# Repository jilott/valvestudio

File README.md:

# valvestudio
All tube projects, laboratory assignments, experiments, etc are here. Go Valves Baby!

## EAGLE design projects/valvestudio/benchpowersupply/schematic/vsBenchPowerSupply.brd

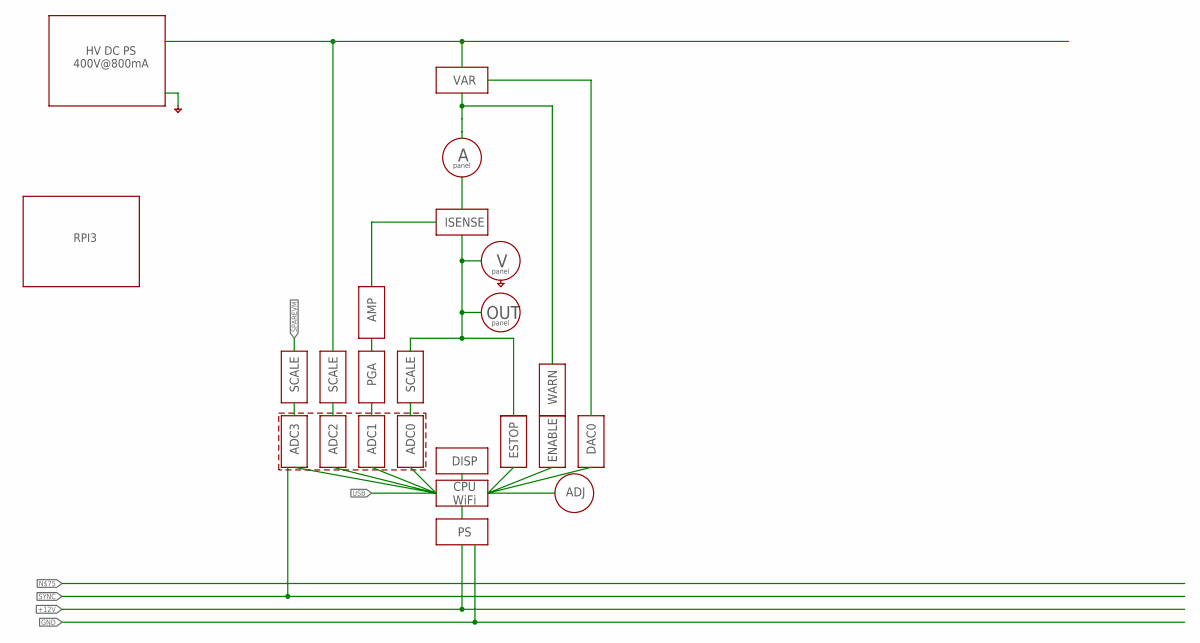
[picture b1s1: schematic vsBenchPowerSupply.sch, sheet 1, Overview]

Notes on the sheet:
HV DC PS 400V@800mA
RPI3
ISENSE
OUT
VAR
DAC0
AMP
ADC1
SCALE
ADC0
WARN
ENABLE
ESTOP
CPU WiFi
ADJ
DISP
ADC3
ADC2
PGA
panel

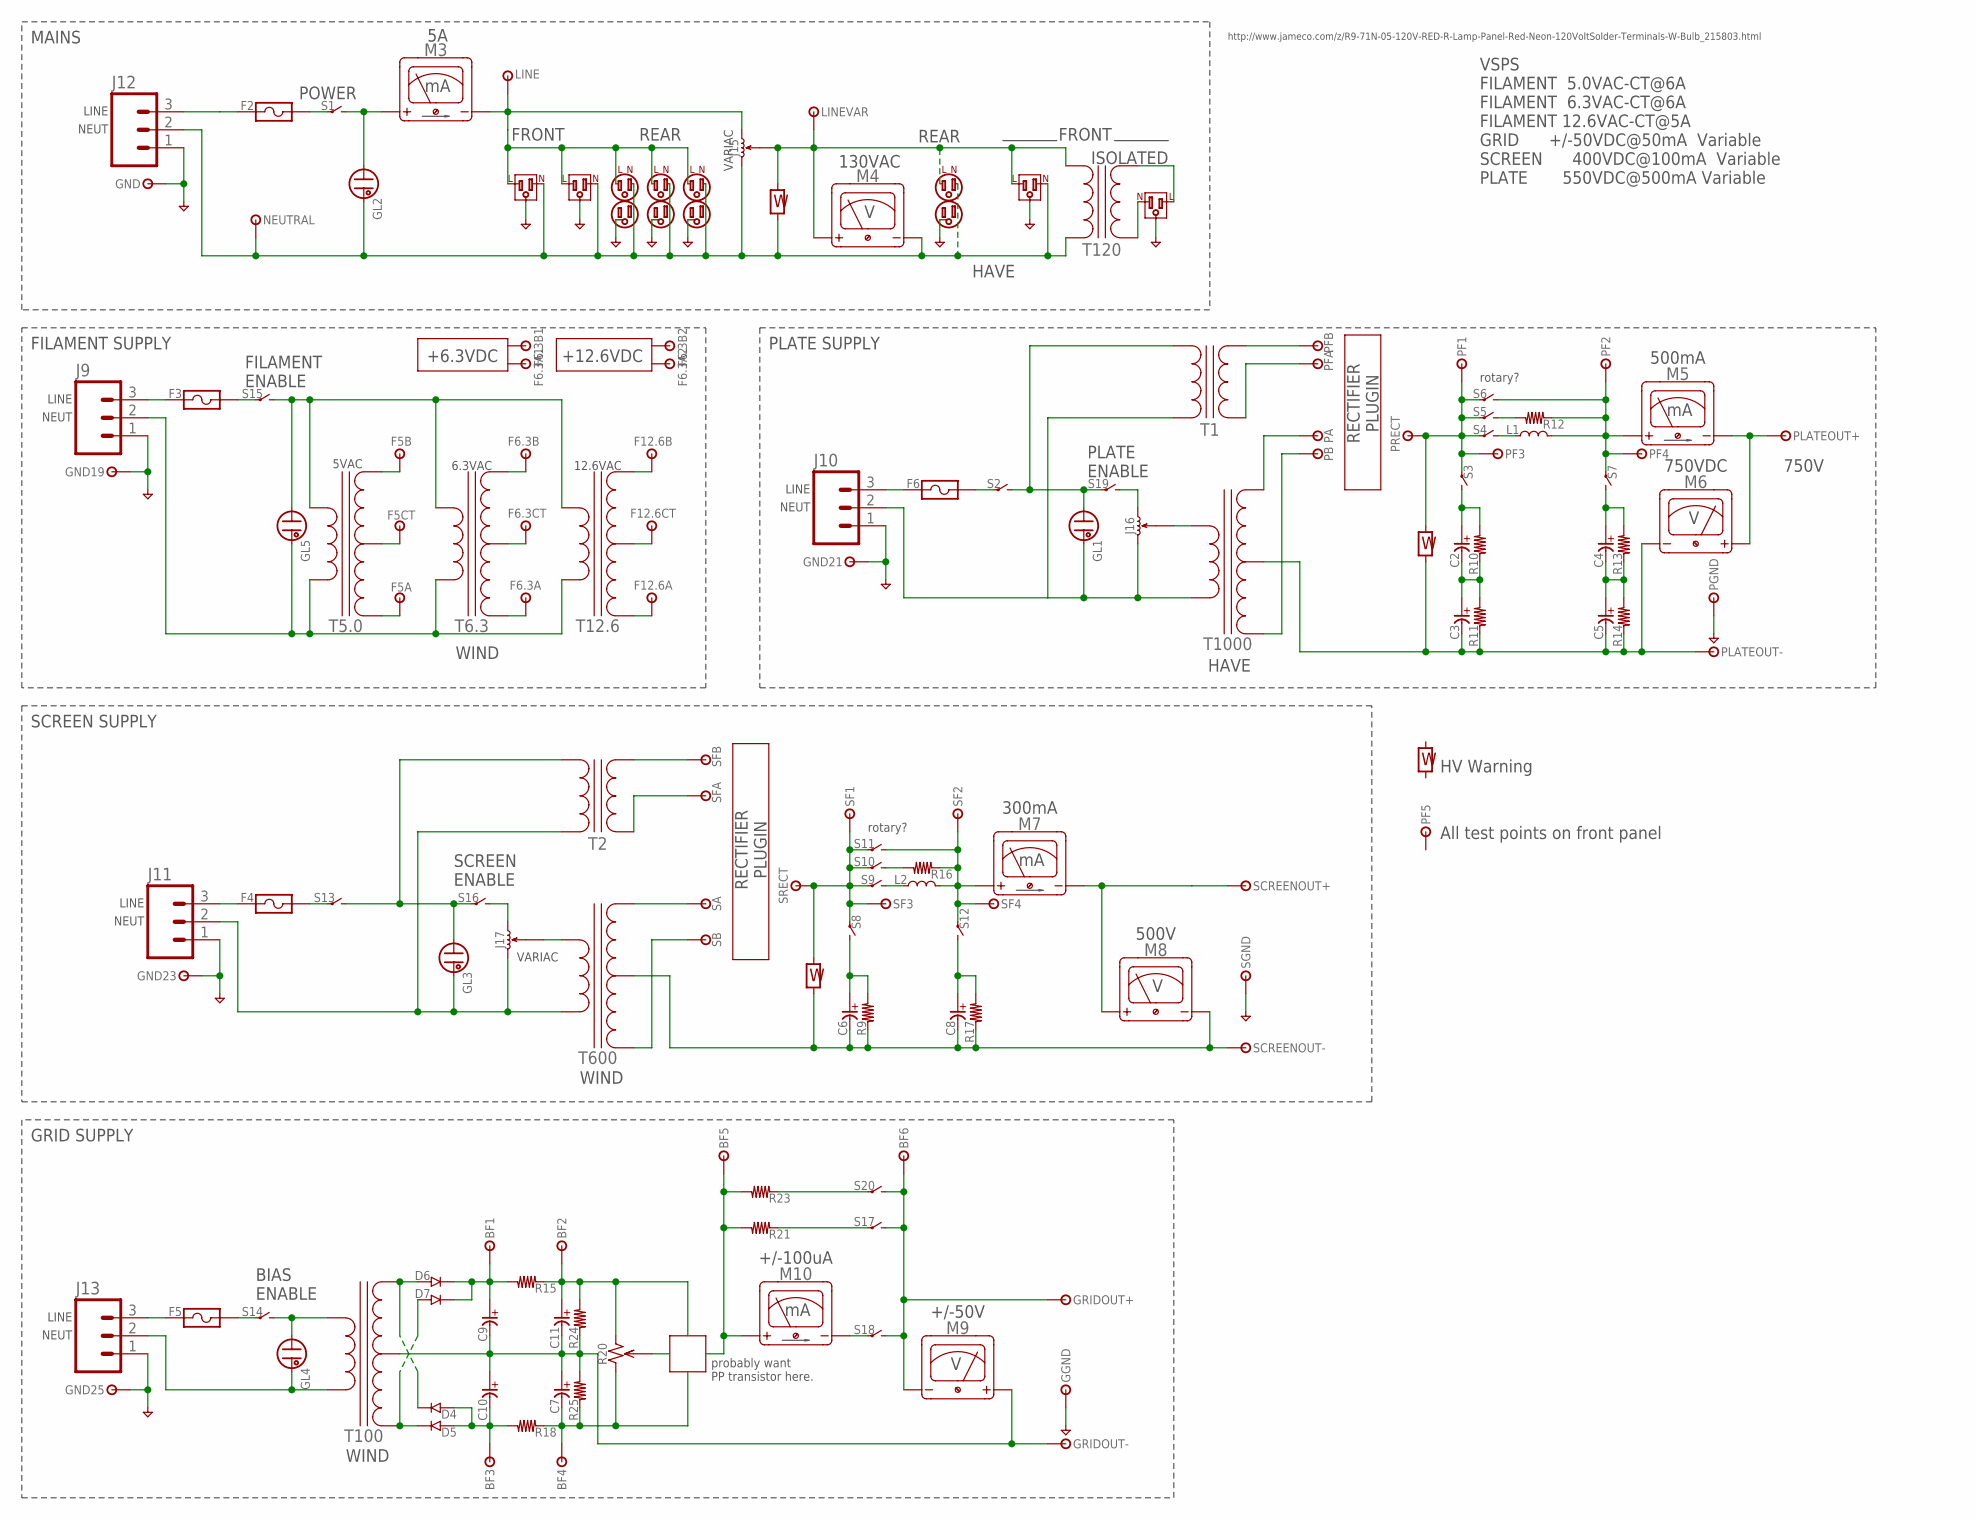
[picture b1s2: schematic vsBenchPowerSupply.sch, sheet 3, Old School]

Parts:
BF1, BF2, BF3, BF4, BF5, BF6: TESTPOINTTHRU; TPTHRU
C2, C3, C4, C5, C6, C7, C8, C9, C10, C11: C-POLARIZED-SMD-E-3MM; E-3
D4, D5, D6, D7: DIODE-1N4148; DO-35
F2, F3, F4, F5, F6: FUSE-HOLDER-3557-2; 3557-2
F5A, F5B, F5CT, F6.3A, F6.3A1, F6.3A2, F6.3B, F6.3B1, F6.3B2, F6.3CT, F12.6A, F12.6B, F12.6CT: TESTPOINTTHRU; TPTHRU
GGND: TESTPOINTTHRU; TPTHRU
GL1, GL2, GL3, GL4, GL5: INDICATOR-NEON-BULB-NE2-DRILL; NE2-NEON-BULB-DRILL
GND, GND19, GND21, GND23, GND25: TESTPOINTTHRU; TPTHRU
GRIDOUT+: TESTPOINTTHRU; TPTHRU
GRIDOUT-: TESTPOINTTHRU; TPTHRU
J3, J4, J5, J18: OUTLET-RECEPTABLE-SINGLE; CONN-3.81MM-KF2EDG-3
J6, J7, J8, J14: METER-PANEL-HV-WARNING; CONN-.100-2
J9, J10, J11, J12, J13: CONN-03-3.81MM-PLUGIN-SCREW; CONN-3.81MM-KF2EDG-3
J15, J16, J17: VARIAC; CONN-.100-3
L1, L2: INDUCTOR-0805; R0805
LINE: TESTPOINTTHRU; TPTHRU
LINEVAR: TESTPOINTTHRU; TPTHRU
M3, M5, M7, M10: METER-PANEL-ANALOG-CURRENT-PLUGIN-3.81MM; CONN-3.81MM-KF2EDG-2
M4, M6, M8, M9: METER-PANEL-ANALOG-VOLTAGE-PLUGIN-3.81MM; CONN-3.81MM-KF2EDG-2
NEUTRAL: TESTPOINTTHRU; TPTHRU
PA: TESTPOINTTHRU; TPTHRU
PB: TESTPOINTTHRU; TPTHRU
PF1, PF2, PF3, PF4, PF5: TESTPOINTTHRU; TPTHRU
PFA: TESTPOINTTHRU; TPTHRU
PFB: TESTPOINTTHRU; TPTHRU
PGND: TESTPOINTTHRU; TPTHRU
PLATEOUT+: TESTPOINTTHRU; TPTHRU
PLATEOUT-: TESTPOINTTHRU; TPTHRU
PRECT: TESTPOINTTHRU; TPTHRU
R9, R10, R11, R12, R13, R14, R15, R16, R17, R18, R21, R23, R24, R25: R-0402; R0402
R20: POTENTIOMETER; CONN-.100-3
S1, S2, S3, S4, S5, S6, S7, S8, S9, S10, S11, S12, S13, S14, S15, S16, S17, S18, S19, S20: SWITCH-PANEL-SPST; CONN-.100-2
SA: TESTPOINTTHRU; TPTHRU
SB: TESTPOINTTHRU; TPTHRU
SCREENOUT+: TESTPOINTTHRU; TPTHRU
SCREENOUT-: TESTPOINTTHRU; TPTHRU
SF1, SF2, SF3, SF4: TESTPOINTTHRU; TPTHRU
SFA: TESTPOINTTHRU; TPTHRU
SFB: TESTPOINTTHRU; TPTHRU
SGND: TESTPOINTTHRU; TPTHRU
SRECT: TESTPOINTTHRU; TPTHRU
T1, T2, T120: TRANSFORMER-2-2; TRANSFORMER-4-2-G
T5.0, T6.3, T12.6, T100, T600, T1000: TRANSFORMER-3-2; CONN-.100-5
U$1, U$2, U$3, U$4: OUTLET-RECEPTACLE; CONN-3.81MM-KF2EDG-3

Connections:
BIASOUT: BF6.1, GRIDOUT+.1, M9.1 (-), S17.2, S18.2, S20.2
F6.3B: F6.3B.1, T6.3.3 (P1)
GND: GGND.1, GND.1, GND19.1, GND21.1, GND23.1, GND25.1, J3.1 (GND), J4.1 (GND), J5.1 (GND), J9.1, J10.1, J11.1, J12.1, J13.1, J18.1 (GND), PGND.1, SGND.1, U$1.1 (GND), U$2.1 (GND), U$3.1 (GND), U$4.1 (GND); also elsewhere on the board
HVOUT: M5.1 (-), M6.2 (+), PLATEOUT+.1
LINE: J3.3 (LINE), J15.3 (2), J18.3 (LINE), LINE.1, M3.1 (-), U$1.3 (LINE), U$2.3 (LINE), U$3.3 (LINE)
LINEVAR: J5.3 (LINE), J6.1, J15.2 (W), LINEVAR.1, M4.2 (+), T120.1, U$4.3 (LINE)
unnamed: C2.+, R10.2, S3.2
unnamed: L1.1, M5.2 (+), PF2.1, PF4.1, R12.1, S6.2, S7.1
unnamed: C2.-, C3.+, R10.1, R11.2
unnamed: L1.2, S4.2
unnamed: R12.2, S5.2
unnamed: J17.2 (W), T600.1 (S1)
unnamed: C4.+, R13.2, S7.2
unnamed: GL1.1 (A), S2.2, S19.1, T1.1
unnamed: C4.-, C5.+, R13.1, R14.2
unnamed: F2.1@1, F2.1@2, J12.3
unnamed: GL3.1 (A), S13.2, S16.1, T2.1
unnamed: C6.+, R9.2, S8.2
unnamed: F2.2@1, F2.2@2, S1.1
unnamed: GL5.1 (A), S15.2, T5.0.1 (S1), T6.3.1 (S1), T12.6.1 (S1)
unnamed: GL2.1 (A), M3.2 (+), S1.2
unnamed: L2.2, S9.2
unnamed: BF5.1, M10.2 (+), R21.2, R23.2
unnamed: D5.C, D7.A, T100.5 (P2)
unnamed: R16.2, S10.2
unnamed: C8.+, R17.2, S12.2
unnamed: J4.3 (LINE), T120.5 (S1)
unnamed: BF2.1, C11.+, R15.1, R20.3 (2), R24.2
unnamed: L2.1, M7.2 (+), R16.1, S11.2, S12.1, SF2.1, SF4.1
unnamed: R21.1, S17.1
unnamed: BF1.1, C9.+, D6.C, D7.C, R15.2
unnamed: J4.2 (NEU), T120.6 (S2)
unnamed: F5.2@1, F5.2@2, S14.1
unnamed: GL4.1 (A), S14.2, T100.1 (S1)
unnamed: F3.1@1, F3.1@2, J9.3
unnamed: F4.2@1, F4.2@2, S13.1
unnamed: F6.1@1, F6.1@2, J10.3
unnamed: F3.2@1, F3.2@2, S15.1
unnamed: BF3.1, C10.-, D4.A, D5.A, R18.2
unnamed: F5.1@1, F5.1@2, J13.3
unnamed: F6.2@1, F6.2@2, S2.1
unnamed: J16.2 (W), T1000.1 (S1)
unnamed: J17.3 (2), S16.2
unnamed: PFB.1, T1.5 (S1)
unnamed: PFA.1, T1.6 (S2)
unnamed: J16.3 (2), S19.2
unnamed: M10.1 (-), S18.1
unnamed: SFB.1, T2.5 (S1)
unnamed: SFA.1, T2.6 (S2)
unnamed: F4.1@1, F4.1@2, J11.3
unnamed: BF4.1, C7.-, R18.1, R20.1, R25.1
unnamed: C7.+, C9.-, C10.+, C11.-, GRIDOUT-.1, M9.2 (+), R24.1, R25.2, T100.4 (PCT)
unnamed: D4.C, D6.A, T100.3 (P1)
unnamed: R23.1, S20.1
NEUTRAL: GL1.2 (A1), GL2.2 (A1), GL3.2 (A1), GL4.2 (A1), GL5.2 (A1), J3.2 (NEU), J5.2 (NEU), J6.2, J9.2, J10.2, J11.2, J12.2, J13.2, J15.1, J16.1, J17.1, J18.2 (NEU), M4.1 (-), NEUTRAL.1, T1.2, T2.2, T5.0.2 (S2), T6.3.2 (S2), T12.6.2 (S2), T100.2 (S2), T120.2, T600.2 (S2), T1000.2 (S2), U$1.2 (NEU), U$2.2 (NEU), U$3.2 (NEU), U$4.2 (NEU)
PA: PA.1, T1000.3 (P1)
PB: PB.1, T1000.5 (P2)
PLATECT: C3.-, C5.-, J7.2, M6.1 (-), PLATEOUT-.1, R11.1, R14.1, T1000.4 (PCT)
PRECT: J7.1, PF1.1, PF3.1, PRECT.1, S3.1, S4.1, S5.1, S6.1
SA: SA.1, T600.3 (P1)
SB: SB.1, T600.5 (P2)
SCREENCT: C6.-, C8.-, J8.2, M8.1 (-), R9.1, R17.1, SCREENOUT-.1, T600.4 (PCT)
SCREENOUT: M7.1 (-), M8.2 (+), SCREENOUT+.1
SRECT: J8.1, S8.1, S9.1, S10.1, S11.1, SF1.1, SF3.1, SRECT.1
VFIL5A: F5A.1, T5.0.5 (P2)
VFIL5B: F5B.1, T5.0.3 (P1)
VFIL5CT: F5CT.1, T5.0.4 (PCT)
VFIL6A: F6.3A.1, T6.3.5 (P2)
VFIL6CT: F6.3CT.1, T6.3.4 (PCT)
VFIL12A: F12.6A.1, T12.6.5 (P2)
VFIL12B: F12.6B.1, T12.6.3 (P1)
VFIL12CT: F12.6CT.1, T12.6.4 (PCT)

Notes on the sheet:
LINE
NEUT
5VAC
VARIAC
6.3VAC
12.6VAC
http://www.jameco.com/z/R9-71N-05-120V-RED-R-Lamp-Panel-Red-Neon-120VoltSolder-Terminals-W-Bulb_215803.html
PLATE ENABLE
POWER
RECTIFIER PLUGIN
SCREEN ENABLE
VSPS FILAMENT 5.0VAC-CT@6A FILAMENT 6.3VAC-CT@6A FILAMENT 12.6VAC-CT@5A GRID +/-50VDC@50mA Variable SCREEN 400VDC@100mA Variable PLATE 550VDC@500mA Variable
BIAS ENABLE
ISOLATED
130VAC
300mA
500V
500mA
750V
+/-50V
FILAMENT ENABLE
+/-100uA
FRONT
REAR
HAVE
WIND
MAINS
FILAMENT SUPPLY
PLATE SUPPLY
SCREEN SUPPLY
GRID SUPPLY
rotary?
HV Warning
probably want PP transistor here.
+6.3VDC
+12.6VDC
All test points on front panel
750VDC

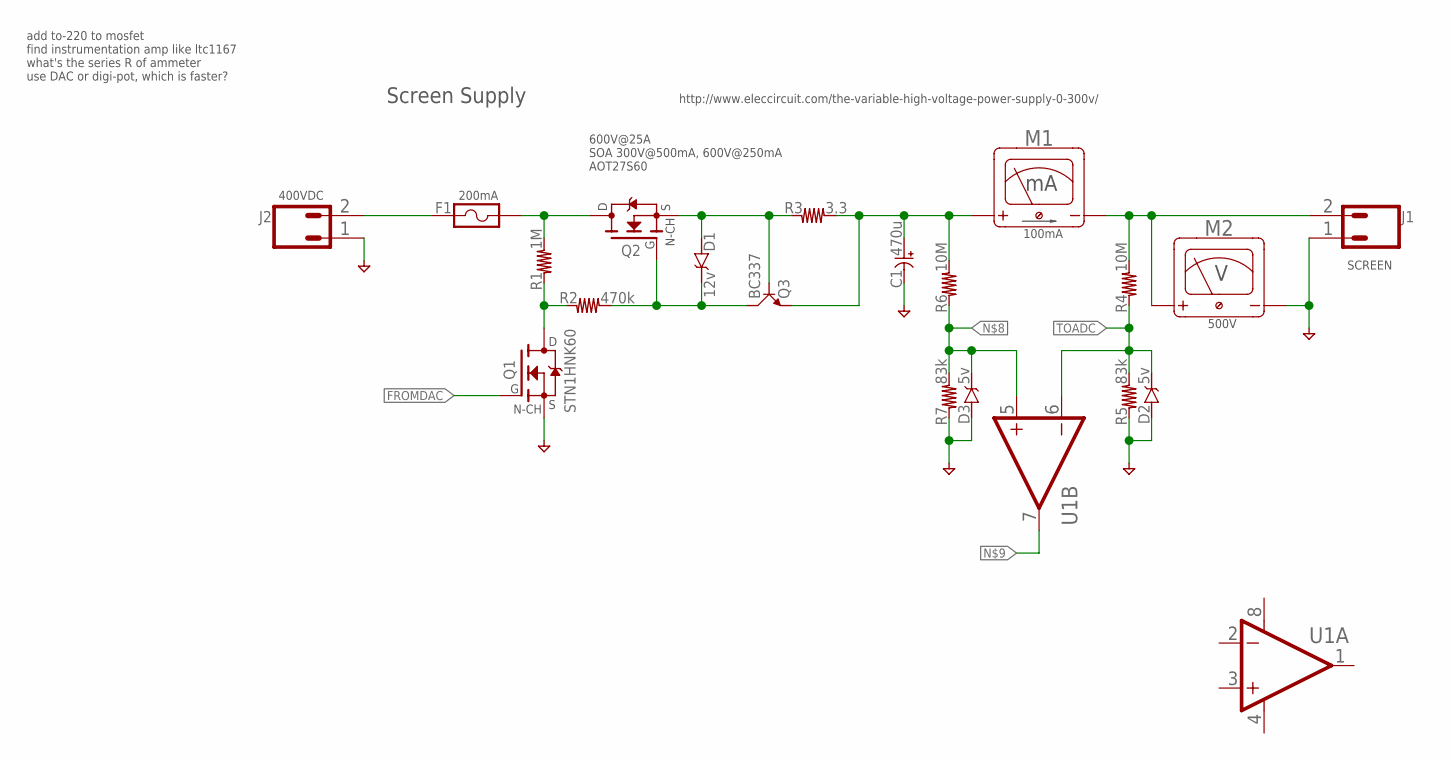
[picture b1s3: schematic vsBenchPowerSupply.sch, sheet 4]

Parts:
C1: 470u; E5-10,5
D1: 12v; SOD-323
D2, D3: 5v; SOD-323
F1: FUSE-HOLDER-3557-2; 3557-2
J1, J2: CONN-02-3.81MM-PLUGIN-SCREW; CONN-3.81MM-KF2EDG-2
M1: METER-PANEL-ANALOG-CURRENT-PLUGIN-3.81MM; CONN-3.81MM-KF2EDG-2
M2: METER-PANEL-ANALOG-VOLTAGE-PLUGIN-3.81MM; CONN-3.81MM-KF2EDG-2
Q1: STN1HNK60; SOT23-3
Q2: FET-NCH-TO252; TO252
Q3: BC337; SOT23-3
R1: 1M; R2512
R2: 470k; R2512
R3: 3.3; R2512
R4, R6: 10M; R2512
R5, R7: 83k; R2512
U1: AMP-OPAMP-DUAL-SO08; SO08

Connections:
FROMDAC: Q1.1 (G)
GND: C1.- (2), D2.A, D3.A, J1.1, J2.1, M2.1 (-), Q1.2 (S), R5.1, R7.1; also elsewhere on the board
unnamed: J1.2, M1.1 (-), M2.2 (+), R4.2
unnamed: D1.A, Q2.2 (S), Q3.1 (B), R3.1
unnamed: C1.+ (1), M1.2 (+), Q3.2 (E), R3.2, R6.2
unnamed: D1.C, Q2.1 (G), Q3.3 (C), R2.2
unnamed: F1.1@1, F1.1@2, J2.2
unnamed: Q1.3 (D), R1.1, R2.1
unnamed: F1.2@1, F1.2@2, Q2.3 (D), R1.2
unnamed: D3.C, R6.1, R7.2, U1.5 (+IN)
TOADC: D2.C, R4.1, R5.2, U1.6 (-IN)
V+: U1.8 (V+)
V-: U1.4 (V-)

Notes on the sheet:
SCREEN
100mA
500V
600V@25A SOA 300V@500mA, 600V@250mA AOT27S60
http://www.eleccircuit.com/the-variable-high-voltage-power-supply-0-300v/
Screen Supply
400VDC
200mA
add to-220 to mosfet find instrumentation amp like ltc1167 what's the series R of ammeter use DAC or digi-pot, which is faster?

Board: 2 copper layers, 173 parts (0 on the bottom side), 81 nets, no tracks yet.

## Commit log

2016-03-07 initial add
2016-03-09 fixed a few things
2016-03-28 initial add for cad and www
2016-03-28 good enough for now
2016-04-08 simulation files for inductor measurement
2016-04-09 fixed some typoes, add L calc at end
2016-04-09 more clean up on ipy notebook
2016-04-09 release used in 160409 video
2016-04-09 renamed file
2016-04-15 added koren's triode model
2016-04-16 added koren model to triode and pentode, pentode not functional yet
2016-04-16 koren model now functional added a combined vanderveen and koren comparison plot
2016-04-16 now plotting all the curves
2016-04-23 initial add for loadline visualization
2016-04-24 initial add for notebook file changed header in csv
2016-04-24 fixed typos
2016-04-24 initial add for jpgs
    mectron now has faster slider response and better title, loadline highlight
2016-04-24 added annotations to graph points
2016-04-24 put an angle on the annotation arrows
2016-04-28 added transfer curve, transient calc and fft for distortion
2016-04-28 fixed a couple typoes
2016-04-28 added more points in engauge, changed fn extension
2016-04-28 added sound playback in js
2016-04-29 cleaned up text, added reference section added voltages and currents to schematic
2016-04-29 added fft freq peak detection
2016-04-30 updated drawing with measured voltages and currents transfer characterist now fsolves for Vg
2016-04-30 file re-org
2016-05-01 triode version now functional
2016-05-01 working versions except for artwork and images
2016-05-01 testing something
2016-05-01 a little more fix up
2016-05-03 added 16Vpp drive for audio playback section
2016-05-03 put the q point back in position
2016-05-27 project name change
2016-05-29 pentode, reworked transient power calculation
2016-05-30 fixed distortion calculation
2016-06-03 now with trig function support in functions
2016-06-29 initial add for marshall, don't know the the rest
2016-06-29 deleting this from repo
2016-07-03 initial add for loadline
2016-07-04 working version for PP load line
2016-07-04 saved back to default
2016-07-12 just collecting docs
2016-08-02 initial add, mostly committing my fullerton work for the past week or so
2016-12-20 don't know what's changed
2016-12-23 massive change to structure, added classes, support for multiple windings, support for winding order
2017-01-10 added winding order and more fixes added examples to notebook
2017-01-10 added more examples to notebook cleaned up some formatting
2017-01-10 rewrote the windings section of the report
2017-01-11 added support for fluxtable sorting
2017-01-11 added fluxTable sort by error
2017-01-11 fixed ohms/1000' error in the wire table
2017-01-12 updated compute, now more accurate MPL, resistance, vdrop
2017-01-12 just playing around
2017-01-12 revised gcode generation
2017-01-15 a bunch of tweaks
2017-01-15 first working version of machine control
2017-01-16 added switch support added linear xy jogging to wind manually added wire selection
2017-01-16 gcode revision
2017-01-16 revised gcode added help screen added wind/leadin toggle moved linear operation to 'Z' button
2017-01-17 added winding support to machine initial add for sending config to new grbl
2017-01-17 re-arranged the order of the wind loop
2017-01-17 fixed tap position errors fixed tap where tape point occurs on different layer
2017-01-17 added fillLast support
2017-01-20 updated todo added a route plot
2017-01-20 added argc check
2017-01-20 added equations to notebook corrected errors in loss and temperature rise
2017-01-20 revised weight, loss and temperature rise added plot method to Transformer
2017-01-20 tweaked plotting gcode() now returns nc and doesn't print it
2017-01-23 added support for continuous rotation on x direction change
2017-01-23 working on flow control, 600*.py fails with buffer overflow
2017-01-24 changed the windingWind method, now has a statemap that marches through the route more efficiently with better flow control
2017-01-25 added winding info redraw during winding fixed last leg finished indicator
2017-01-25 added screen clear on exits
2017-01-26 added leakage todo items machine '+','-' now only change override when state==run
2017-01-26 merge
2017-01-26 added some labels
2017-01-26 skipping notebook checkpoints
2017-01-30 added to notebook for 170130 video
2017-01-31 reordered comments in notebook added examples added wolpert design
2017-02-05 initial add for most
2017-02-06 fixing Machine so tranformerdesigner works in notebook without pyserial
2017-02-06 fixing import
2017-04-05 big submit, should do this more often, duh!
2017-06-01 initial add for most little tweaks for rest
2017-06-02 added line labels and colors
2017-07-07 added new project: operatingPowerDesign
2017-07-07 added -80dB noise to signal
2017-08-05 changed params on examples re-ordered the transformer print to find vout portion easier
2017-08-12 added grbl config method
2017-08-12 had this somewhere from some reason
2017-08-13 added command C for grbl config
2017-09-11 initial add imd example shows a muddy Gmaj triad
2017-11-06 img/imd.py moved to imd-300-400.py imd/imd.py now has sliders wiretable now has diameter_mm column
2017-11-06 even1 offset = 1.0
2017-11-06 added linear clean and even1, title, removed some gain options
2017-11-27 added "main" section to milo solve now prints complete input and output table
2018-05-29 moved import termios into try block
2018-06-05 added bias slider and fixed transfer plot
2018-06-06 fixed transfer plot, gain,bias,offset,level now work correctly changed autoscaling option to not tight vin plot is now offset-level corrected play_out is now using correct data array
2018-06-06 added annoutation to fft, only shows when peak count less that 20
2018-06-06 initial add for docs removed autoscaling on transfer plot added annotations to fft plot
2020-04-13 re-org
2020-04-13 updated notebook for python3 and moved notes to README
2020-04-13 updated a couple things
2020-04-13 added engauge screenshot
2020-04-14 added screen current support
2020-04-15 fixing the fft graph
2020-04-15 harmonic analysis now functional
2020-04-18 added ability to scale screen voltage
2020-04-18 added schematic and datasheets specs
2020-04-18 added grid bias voltage to plot bubble
2020-04-18 after run all and toggle code off
2020-04-18 reordered the refs
2020-04-18 doing push before video record
2020-04-18 typo
2020-04-19 updated schematic png
2020-04-19 added alt-t support for code toggle
2020-04-19 increased Va limit to 400
2020-04-19 added screen resistor and capacitor
2020-04-19 changes for video
2020-04-19 added power supply resistance dependence on plate voltage
2020-04-19 worked on fft display
2020-04-19 corrected the power supply and output resistance, Vb calculation
2020-04-20 commit for video part 1
2020-04-20 fixed the screen voltage actual and the screen resistor calculation
2021-03-11 added images
